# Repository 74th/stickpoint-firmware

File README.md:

# StickPoint Firmware

Pointer module with joystick.

ジュイスティックを使ったポインターモジュール

> [!IMPORTANT]
> This module does not replicate the feel of Trackpoint. このモジュールはトラックポイントの操作性を再現するものではありません。

> [!IMPORTANT]
> KiCad ファイルのスナップショットも含まれていますが、Booth での購入など作者 74th から入手したもののみサポートします。

On sale at Booth. Booth にて販売中 https://74th.booth.pm/items/5404009

## features / 特徴

- I2C connection, Pimoroni Trackball module PIM447 compatible
- Grove I2C socket for M5Stack etc.
- Double speed mode by moving the trackball twice (ex: ←, center, ←)

### Japanese

- I2C 接続、Pimoroni Trackball モジュール PIM447 互換
- Grove の I2C ソケットをもち、M5Stack などを接続可能
- 2 回、コツコツと、←、中央、← の用に動かすと、倍速モードになります

## I2C Interface / I2C インターフェイス

Connect the I2C Grove port or the through-hole on the board to a port on the microcontroller where I2C is available. I2C Grove ポート、もしくは基板のスルーホールを、マイコンの I2C が利用できるポートに接続してください。

### StickPointV v1.1.0

I2C の SDA、SCL は、モジュール内で 1kΩ 抵抗で VCC 電圧にプルアップされています。

### StickPointV v1.0.0

Note that I2C SDA and SCL require a pull-up. RP2040 requires an external pull-up resistor of about 1 kΩ. When operating at 3.3 V, connect a 1 kΩ resistor between the 3.3 V supply and SDA and SCL. なお、I2C の SDA、SCL にはプルアップが必要です。RP2040 では外部の 1kΩ 程度のプルアップ抵抗が必要になります。3.3V で動作させる場合は、3.3V 電源と、SDA、SCL の間に 1kΩ の抵抗を接続してください。

## I2C Protocol / I2C 通信仕様

Address: 0x0A

When a send instruction is issued, the following 5 bytes are returned. 送信指示を出すと、以下の 5 バイトを返します。

- 1: left
- 2: right
- 3: down
- 4: up
- 5: 0

## Documents

- StickPointV (CH32V003)
  - v1.1.0
    - Semantics: [PDF](docs/stickpointv-ch32v003-v1.1.0-semantics.pdf), [KiCanvas](https://kicanvas.org/?github=https%3A%2F%2Fgithub.com%2F74th%2Fstickpoint-firmware%2Fblob%2Fmain%2Fdocs%2Fstickpointv-ch32v003-v1.1.0-semantics.kicad_sch), [kicad_sch](./docs/stickpointv-ch32v003-v1.1.0-semantics.kicad_sch)
    - PCB: [KiCanvas](https://kicanvas.org/?github=https%3A%2F%2Fgithub.com%2F74th%2Fstickpoint-firmware%2Fblob%2Fmain%2Fdocs%2Fstickpointv-ch32v003-v1.1.0-pcb.kicad_pcb)
    - changed
      - add I2C pull-up resistor
      - add Qwiic connector
  - v1.0.0
    - Semantics: [PDF](docs/stickpointv-ch32v003-v1.0.0-semantics.pdf), [KiCanvas](https://kicanvas.org/?github=https%3A%2F%2Fgithub.com%2F74th%2Fstickpoint-firmware%2Fblob%2Fmain%2Fdocs%2Fstickpointv-ch32v003-v1.0.0-semantics.kicad_sch), [kicad_sch](./docs/stickpointv-ch32v003-v1.0.0-semantics.kicad_sch)
    - PCB: [KiCanvas](https://kicanvas.org/?github=https%3A%2F%2Fgithub.com%2F74th%2Fstickpoint-firmware%2Fblob%2Fmain%2Fdocs%2Fstickpointv-ch32v003-v1.0.0-pcb.kicad_pcb)
- ⚠︎Deprecated⚠︎ StickPoint (ATTiny402)
  - v1.0.1
    - Semantics: [PDF](docs/stickpoint-attiny402-v1.0.1-semantics.pdf), [KiCanvas](https://kicanvas.org/?github=https%3A%2F%2Fgithub.com%2F74th%2Fstickpoint-firmware%2Fblob%2Fmain%2Fdocs%2Fstickpoint-attiny402-v1.0.1-semantics.kicad_sch), [kicad_pcb](./docs/stickpointv-ch32v003-v1.0.0-pcb.kicad_pcb)
    - PCB: [KiCanvas](https://kicanvas.org/?github=https%3A%2F%2Fgithub.com%2F74th%2Fstickpoint-firmware%2Fblob%2Fmain%2Fdocs%2Fstickpoint-attiny402-v1.0.1-pcb.kicad_pcb)

## How to use QMK Firmware with RP2040 / RP2040 での QMK Firmware での使用方法

Connect SDA and SCL of the module to the I2C capable ports on the RP2040. Also connect GND and VCC (3.3V/5V). RP2040 の I2C が使えるポートに、モジュールの SDA、SCL を接続します。また、GND、VCC（3.3V/5V）も接続してください。

RP2040 には、2 つの I2C の I2C0 と I2C1 があります。どちらを利用するかはポートにより異なります。RP2040 のドキュメントから確認してください。

### rules.mk

Add the following statement. 以下の記述を追加してください。

```
POINTING_DEVICE_ENABLE = yes
I2C_DRIVER_REQUIRED = yes
POINTING_DEVICE_DRIVER = pimoroni_trackball
```

### halconf.h

If halconf.h does not exist, create it and add the following statement. halconf.h がない場合作成して、以下の記述を追加してください。

```
#pragma once

#define HAL_USE_I2C TRUE

#include_next <halconf.h>
```

### mcuconf.h

If mcuconf.h does not exist, create it and add the following statement. mcuconf.h がない場合作成して、以下の記述を追加してください。

The TRUE and FALSE values for RP_I2C_USE_I2C0 and RP_I2C_USE_I2C1 should be changed according to I2C0 and I2C1 used. RP_I2C_USE_I2C0、RP_I2C_USE_I2C1 の TRUE、FALSE は利用する I2C0、I2C1 によって変更してください。

```
#pragma once

#include_next <mcuconf.h>

#undef RP_I2C_USE_I2C0
#define RP_I2C_USE_I2C0 TRUE

#undef RP_I2C_USE_I2C1
#define RP_I2C_USE_I2C1 FALSE
```

### config.h

以下の記述を追加してください。

I2C1_SCL_PIN、I2C1_SDA_PIN には接続した I2C ポートを指定してください。

```
#pragma once

#define PIMORONI_TRACKBALL_ADDRESS 0x0A
#define I2C1_SCL_PIN GP1
#define I2C1_SDA_PIN GP0
#define I2C_DRIVER I2CD0
#define F_SCL 100000
#define PIMORONI_TRACKBALL_SCALE 5
```

Even when I2C0 is used, it seems to be described in I2C1_SCL_PIN and I2C1_SDA_PIN. I2C0 を利用する場合であっても、I2C1_SCL_PIN、I2C1_SDA_PIN に記述するようです。

PIMORONI_TRACKBALL_SCALE is a value that is multiplied by the acquired value. Use it to adjust the amount of movement. PIMORONI_TRACKBALL_SCALE は、取得した値に対してかけ算される値です。移動量の調整に利用してください。

### Scroll / スクロール

The QMK Firmware documentation describes how to implement scrolling by clicking and moving. Please refer to this document. QMK Firmware のドキュメントにはクリックしながら移動するとスクロールする様に実装する方法について記述があります。こちらを参考にしてみてください。

https://docs.qmk.fm/#/feature_pointing_device?id=drag-scroll-or-mouse-scroll

https://docs.qmk.fm/#/feature_pointing_device?id=advanced-drag-scroll

### Example / 例

Sparrow60C https://github.com/74th/qmk_firmware_sparrow_keyboard/tree/sparrow/keyboards/sparrow60c

## How to update Firmware / ファームウェアの更新方法

### StickPointV (CH32V003)

WCH-LinkE is required to use CH32V003. CH32V003 を使用するため、WCH-LinkE が必要です。

WCH-LinkE is available at the following stores. Please note that similar WCH-Link (without E) is not supported. WCH-LinkE は、以下のショップで購入可能です。類似品 WCH-Link(E のないもの) は対応していませんので、ご注意ください。

- WCH-LinkE (秋月電子通商) https://akizukidenshi.com/catalog/g/g118065/
- WCH-LinkE (Aliexpress) https://www.aliexpress.com/item/1005005180653105.html
- CH32V003 Kit (Aliexpress WCH-Official Store) https://www.aliexpress.com/item/1005004895791296.html

Connect the WCH-LinkE to the following 3 ports on the module. WCH-LinkE とモジュールの以下の 3 つのポートを接続してください。

- VCC, 3.3V/5V
- GND
- SWDIO

If the Grove port is already providing power, only the following two ports are needed. Grove ポートで既に電源を供給している場合は、以下の 2 つのポートだけで良いです。

- GND
- SWDIO

This firmware uses ch32v003fun, please refer to the ch32v003fun documentation for how to set up the ch32v003fun development environment. このファームウェアは ch32v003fun を使用しています。ch32v003fun の開発環境の整え方は ch32v003fun のドキュメントを参照して下さい。

https://github.com/cnlohr/ch32v003fun

The software to upload the firmware is minichlink, which is included in ch32v003fun. minichlink should be built and placed in the PATH. ファームウェアをアップロードするソフトウェアには minichlink を使用します。minichlink は ch32v003fun に含まれています。minichlink をビルドしてパスの通る所においてください。

In the stickpointv-ch32v003j4m6 directory, execute the following command. stickpointv-ch32v003j4m6 のディレクトリで、以下のコマンドを実行します。

```
make
```

Fine adjustment of the movement amount is specified by REDUCE_LEVEL. 移動量の微調整は REDUCE_LEVEL で指定します。

### ⚠︎Deprecated⚠︎ StickPoint (ATTiny402)

A UPDI programmer is required to use the ATTiny402. ATTiny402 を使用するため、UPDI プログラマが必要です。
The UPDI programmer can be produced using USB serial conversion. Please check here. UPDI プログラマは、USB シリアル変換を使って制作可能です。こちらを確認ください。

https://github.com/microchip-pic-avr-tools/pymcuprog#serial-port-updi-pyupdi

Use PlatformIO, install the extension PlatformIO in VS Code. PlatformIO を使います。VS Code に拡張機能 PlatformIO をインストールしてください。

Open the stickpoint-attiny402 directory as a workspace in VS Code (open the stickpoint-attiny402 directory with the command "File: Open Folder..."). VS Code で joypoint ディレクトリをワークスペースとして開きます（コマンド「ファイル：フォルダーを開く（File: Open Folder...）」で joypoint ディレクトリを開きます）

Adjust upload_port, upload_command, etc. in platform.ini and upload. platform.ini の upload_port、upload_command などを調整し、アップロードをしてください。

## Tuning Guide / チューニングガイド

The easiest way to tune the amount of movement is to control the amount of movement on the keyboard firmware side; in the case of QMK Firmware, you can set PIMORONI_TRACKBALL_SCALE, a value that is multiplied by the acquired amount of movement. If you want to increase the amount of movement, increase the number; if you want to decrease the amount of movement, decrease the number.

If you want to control the amount of movement in a more detailed manner, there is a value called REDUCE_LEVEL that is controlled on the StickPoint side. The amount of movement is controlled by dividing the calculated amount of movement by this value. If this value is increased, the amount of movement becomes smaller, and if it is decreased, the amount of movement becomes larger.

StickPoint uses the read_analog function to convert the value into a 4-step amount. I did this because I thought that any finer control would be difficult with this device. These thresholds are set by StickPoint's high_zone, deadzone, and middle. Fine tuning can be done by changing this value or changing the value to be set. Currently, the values are converted to four steps of 0, 1, 3, and 5. If you wish to control the values more finely than that, please change them in conjunction with REDUCE_LEVEL.

🇯🇵

最も簡単に移動量をチューニングする方法は、キーボードファームウェア側で移動量を制御することです。QMK Firmware の場合には、PIMORONI_TRACKBALL_SCALE という取得した移動量にかけ算する値を設定できます。移動量を増やしたい場合には数字を大きく、減らしたい場合には小さくしてください。

寄り細かく移動量を制御する場合、StickPoint の側で制御している REDUCE_LEVEL という値があります。算出した移動量にたいして、この値で割ることで移動量を制御しています。この値を大きくすると移動量が小さくなり、小さくすると移動量が大きくなります。

StickPoint は read_analog 関数で、4 段階の量に変換しています。それ以上の細かい制御はこのデバイスでは難しいと、私は考えたためです。この閾値は、StickPoint の high_zone、deadzone、middle で設定しています。この値を変更したり、設定する値を変更することで微調整が可能です。現在は、0、1、3、5 の 4 段階の値に変換していますが、それより細かく制御したい場合は、REDUCE_LEVEL と合わせて変更してください。

## License

MIT License

I would be happy if you would not sell the device. Booth ショップで扱っているため、販売はしないでいただけるとありがたいです。

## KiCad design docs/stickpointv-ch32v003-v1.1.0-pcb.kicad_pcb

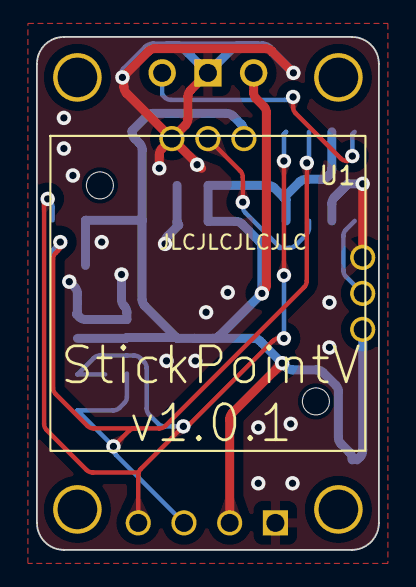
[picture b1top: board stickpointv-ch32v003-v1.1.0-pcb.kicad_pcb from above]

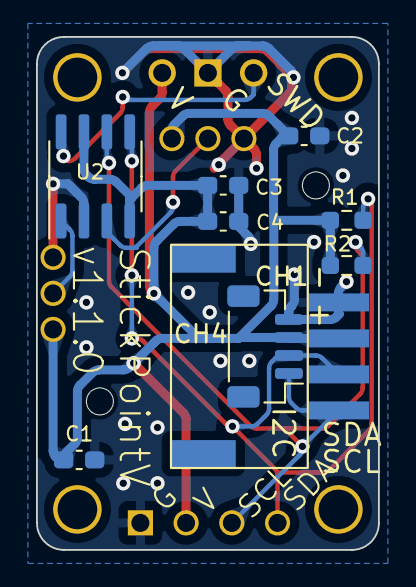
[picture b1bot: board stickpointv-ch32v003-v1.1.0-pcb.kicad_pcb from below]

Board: 2 copper layers, 19.0 x 28.5 mm, 16 parts (11 on the bottom side), 7 nets.

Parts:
C1, C2, C3: 100n; Capacitor_0603_1608
C4: 1u; Capacitor_0603_1608
CH1: I2C; Connector_HY-2.0_SMD_4Pin
CH2: SWD; PinOut_SWD_3Pin
CH3: I2C_Breakout; PinOut_I2C_4Pin
CH4: I2C Qwiic; Connector_SH-1.0_SMD_4Pin
M2, M2#2, M2#3, M2#4: M2_v2
R1, R2: 1k; Register_0603_1608
U1: joystick-b10k; JoyStick_B10K
U2: CH32V003J4M6; SOIC-8_3.9x4.9mm_P1.27mm

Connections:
+3.3V: C1.1, C2.1, C3.1, C4.1, CH1.3 (VCC), CH2.1 (VCC), CH3.2 (VCC), CH4.3 (VCC), R1.1, R2.1, U1.3 (XIN2), U1.4 (YIN1), U2.4 (VDD), U2.7 (PC4)
/SCL: CH1.1 (SCL), CH3.3 (SCL), CH4.1 (SCL), R2.2, U2.6 (PC2)
/SDA: CH1.2 (SDA), CH3.4 (SDA), CH4.2 (SDA), R1.2, U2.5 (PC1)
/SWDIO: CH2.3 (SWD), U2.8 (PD4/PD5/PD1/SWIO)
/XOUT: U1.2 (XOUT), U2.3 (PA2)
/YOUT: U1.5 (YOUT), U2.1 (PD6/PA1)
GND: C1.2, C2.2, C3.2, C4.2, CH1.4 (GND), CH2.2 (GND), CH3.1 (GND), CH4.4 (GND), U1.1 (XIN1), U1.6 (YIN2), U2.2 (GND)

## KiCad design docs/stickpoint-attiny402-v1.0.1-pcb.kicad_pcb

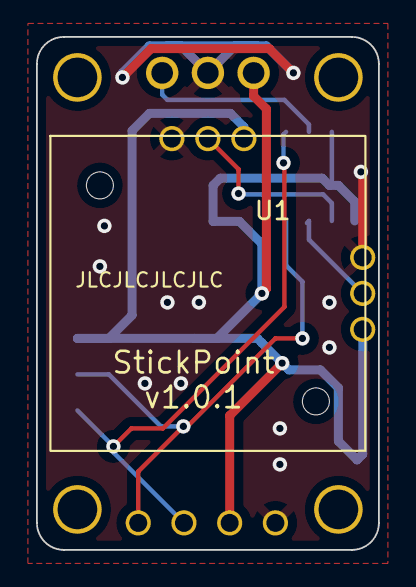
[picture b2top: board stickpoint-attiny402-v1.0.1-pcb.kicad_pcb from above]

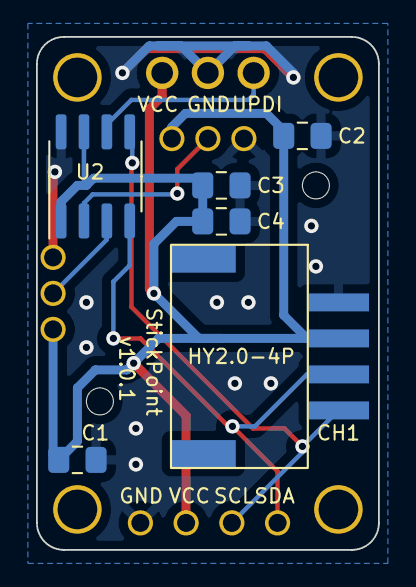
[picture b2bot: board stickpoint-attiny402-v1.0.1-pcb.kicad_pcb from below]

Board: 2 copper layers, 19.0 x 28.5 mm, 13 parts (8 on the bottom side), 7 nets.

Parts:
C1, C2, C3: 100n; Capacitor_0805_2012
C4: 1u; Capacitor_0805_2012
CH1: I2C_Grove; HY2.0_Socket_SMD_4Pin
CH2: UPDI
CH3: I2C_Breakout
M2, M2#2, M2#3, M2#4: M2_v2
U1: joystick-b10k; JOYSTICK-B10K
U2: ATtiny202-SS; SOIC-8_3.9x4.9mm_P1.27mm

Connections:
+3.3V: C1.1, C2.1, C3.1, C4.1, CH1.3 (VCC), CH2.1 (VCC), CH3.2 (VCC), U1.1 (XIN1), U1.4 (YIN1), U2.1 (VCC), U2.7 (PA3)
GND: C1.2, C2.2, C3.2, C4.2, CH1.4 (GND), CH2.2 (GND), CH3.1 (GND), U1.3 (XIN2), U1.6 (YIN2), U2.8 (GND)
SCL: CH1.1 (SCL), CH3.3 (SCL), U2.5 (PA2)
SDA: CH1.2 (SDA), CH3.4 (SDA), U2.4 (PA1)
UPDI: CH2.3 (UPDI), U2.6 (~RESET/PA0)
XOUT: U1.2 (XOUT), U2.2 (PA6)
YOUT: U1.5 (YOUT), U2.3 (PA7)

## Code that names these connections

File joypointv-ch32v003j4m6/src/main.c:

#include "debug.h"
#include "system_ch32v00x.h"

#define XOUT_ADC_CHANNEL ADC_Channel_0
#define YOUT_ADC_CHANNEL ADC_Channel_1
#define V33_ADC_CHANNEL ADC_Channel_2

void init_rcc()
{
    RCC_APB2PeriphClockCmd(RCC_APB2Periph_GPIOC | RCC_APB2Periph_AFIO, ENABLE);
    RCC_APB1PeriphClockCmd(RCC_APB1Periph_I2C1, ENABLE);
    RCC_APB2PeriphClockCmd(RCC_APB2Periph_ADC1, ENABLE);
}

void init_i2c()
{
    GPIO_InitTypeDef GPIO_InitStructure = {0};
    I2C_InitTypeDef I2C_InitTSturcture = {0};

    GPIO_InitStructure.GPIO_Pin = GPIO_Pin_2;
    GPIO_InitStructure.GPIO_Mode = GPIO_Mode_AF_OD;
    GPIO_InitStructure.GPIO_Speed = GPIO_Speed_50MHz;
    GPIO_Init(GPIOC, &GPIO_InitStructure);

    GPIO_InitStructure.GPIO_Pin = GPIO_Pin_1;
    GPIO_InitStructure.GPIO_Mode = GPIO_Mode_AF_OD;
    GPIO_InitStructure.GPIO_Speed = GPIO_Speed_50MHz;
    GPIO_Init(GPIOC, &GPIO_InitStructure);

    I2C_InitTSturcture.I2C_ClockSpeed = 80000;
    I2C_InitTSturcture.I2C_Mode = I2C_Mode_I2C;
    I2C_InitTSturcture.I2C_DutyCycle = I2C_DutyCycle_16_9;
    I2C_InitTSturcture.I2C_OwnAddress1 = 0x02;
    I2C_InitTSturcture.I2C_Ack = I2C_Ack_Enable;
    I2C_InitTSturcture.I2C_AcknowledgedAddress = I2C_AcknowledgedAddress_7bit;
    I2C_Init(I2C1, &I2C_InitTSturcture);

    I2C_Cmd(I2C1, ENABLE);
}

void init_adc()
{
    ADC_InitTypeDef ADC_InitStructure = {0};
    GPIO_InitTypeDef GPIO_InitStructure = {0};

    RCC_ADCCLKConfig(RCC_PCLK2_Div8);

    // PA2 A0 XOUT
    GPIO_InitStructure.GPIO_Pin = GPIO_Pin_2;
    GPIO_InitStructure.GPIO_Mode = GPIO_Mode_AIN;
    GPIO_Init(GPIOA, &GPIO_InitStructure);

    // PA1 A1 YOUT
    GPIO_InitStructure.GPIO_Pin = GPIO_Pin_1;
    GPIO_InitStructure.GPIO_Mode = GPIO_Mode_AIN;
    GPIO_Init(GPIOA, &GPIO_InitStructure);

    // PC4 A2 3.3V
    GPIO_InitStructure.GPIO_Pin = GPIO_Pin_4;
    GPIO_InitStructure.GPIO_Mode = GPIO_Mode_AIN;
    GPIO_Init(GPIOC, &GPIO_InitStructure);

    ADC_DeInit(ADC1);
    ADC_InitStructure.ADC_Mode = ADC_Mode_Independent;
    ADC_InitStructure.ADC_ScanConvMode = DISABLE;
    ADC_InitStructure.ADC_ContinuousConvMode = ENABLE;
    ADC_InitStructure.ADC_ExternalTrigConv = ADC_ExternalTrigConv_None;
    ADC_InitStructure.ADC_DataAlign = ADC_DataAlign_Right;
    ADC_InitStructure.ADC_NbrOfChannel = 1;
    ADC_Init(ADC1, &ADC_InitStructure);

    ADC_Calibration_Vol(ADC1, ADC_CALVOL_50PERCENT);
    // ADC_DMACmd(ADC1, ENABLE);
    ADC_Cmd(ADC1, ENABLE);
    ADC_ResetCalibration(ADC1);
    while (ADC_GetResetCalibrationStatus(ADC1))
        ;
    ADC_StartCalibration(ADC1);
    while (ADC_GetCalibrationStatus(ADC1))
        ;
}

uint16_t read_adc(uint8_t channel)
{
    ADC_RegularChannelConfig(ADC1, channel, 1, ADC_SampleTime_3Cycles);
    ADC_SoftwareStartConvCmd(ADC1, ENABLE);
    ADC_ClearFlag(ADC1, ADC_FLAG_EOC);
    while (ADC_GetFlagStatus(ADC1, ADC_FLAG_EOC) == RESET)
        ;
    return ADC_GetConversionValue(ADC1);
}

int main(void)
{
    NVIC_PriorityGroupConfig(NVIC_PriorityGroup_2);
    Delay_Init();
    init_rcc();
    init_i2c();
    init_adc();
#ifdef CH32V003F4
    USART_Printf_Init(115200);
#endif

    Delay_Ms(100);

    while (1)
    {
        uint16_t xout_adc_value = read_adc(XOUT_ADC_CHANNEL);
        uint16_t yout_adc_value = read_adc(YOUT_ADC_CHANNEL);
        uint16_t v33_adc_value = read_adc(V33_ADC_CHANNEL);
#ifdef CH32V003F4
        printf("XOUT: %d, YOUT: %d, V33: %d\r\n", xout_adc_value, yout_adc_value, v33_adc_value);
#endif
        Delay_Ms(1000);
    }
}

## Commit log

2023-03-05 turned
2023-03-05 add License
2023-03-05 turning
2023-07-23 rename
2023-07-23 ch32v003
2023-07-24 add adc
2023-07-24 dma works
2023-07-29 using ch32v003
2023-07-29 it works
2023-07-29 fix direction
2023-08-05 update README and rename
2023-08-12 remove unused arguments
2024-01-06 for QMK
2024-01-06 turn around to face the other way
2024-01-06 update document
2024-01-07 add pull-up
2024-01-07 add booth shop
2024-01-25 update AKIZUKI URL
2024-11-16 firmware binary
